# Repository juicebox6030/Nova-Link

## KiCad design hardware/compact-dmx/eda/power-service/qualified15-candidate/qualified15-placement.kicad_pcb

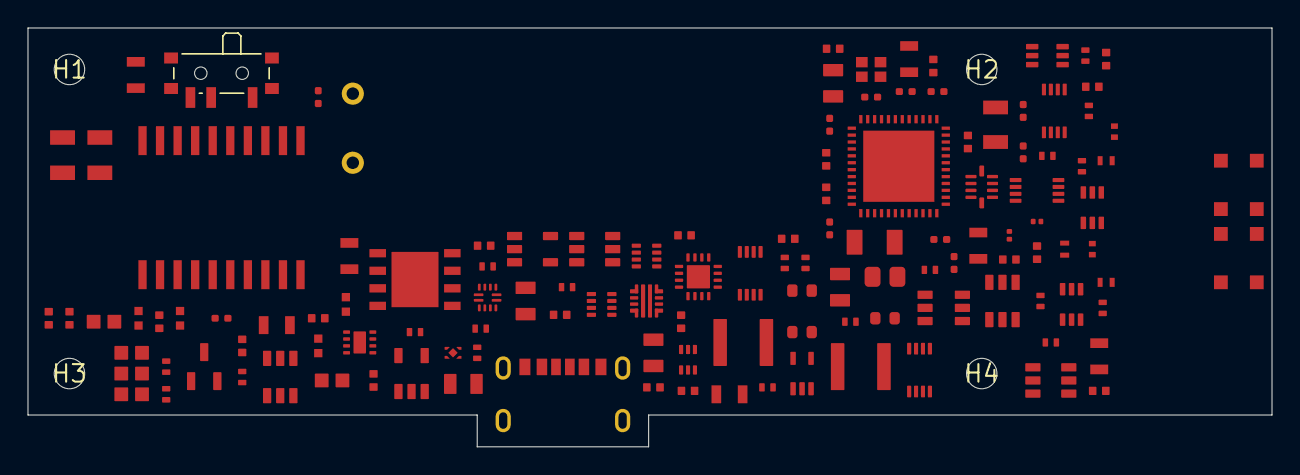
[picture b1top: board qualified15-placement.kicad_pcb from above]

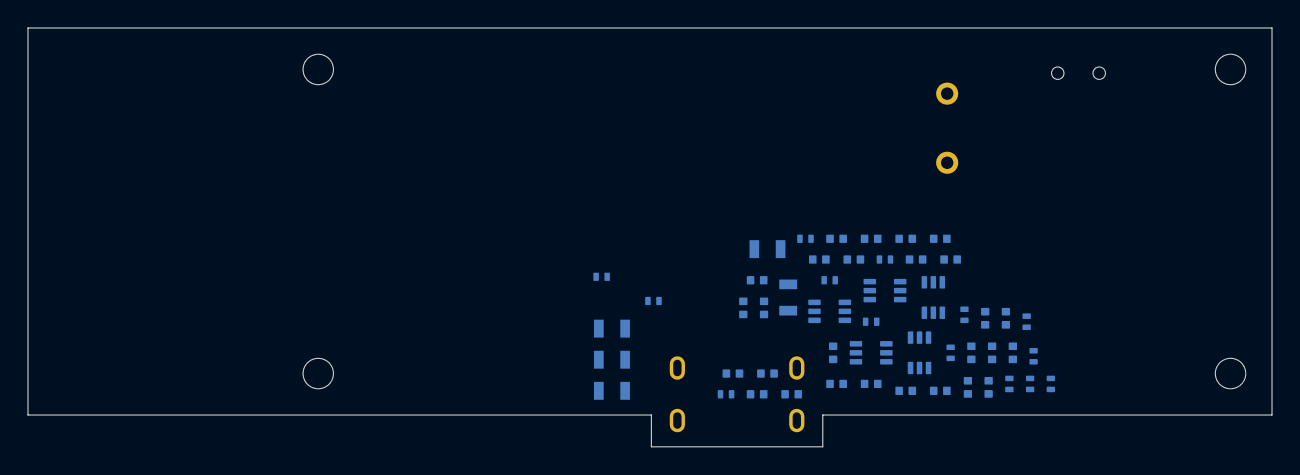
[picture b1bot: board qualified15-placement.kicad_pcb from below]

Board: 2 copper layers, 90.0 x 30.3 mm, 178 parts (51 on the bottom side), 105 nets, no tracks yet.

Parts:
BASE_A101: 0900AD47A2450001E PROTOTYPE TUNING REQUIRED; Johanson_0900AD47_IsolatedLands
BASE_C1, BASE_C3: GRM155R71E104KE14D 100nF 25V X7R; TI_CAPC1005_Vector
BASE_C2, BASE_C4: GRM21BR71A106KE51L 10uF 10V X7R; Murata_GRM21_Reflow
BASE_C101, BASE_C102: GRM188R60J226MEA0D 22uF; TI_CAPC1608_Vector
BASE_C103: GRM155R61C105KA12D 1uF; TI_CAPC1005_Vector
BASE_C104, BASE_C105, BASE_C106, BASE_C107, BASE_C108, BASE_C109: GRM155R71E104KE14D 100nF; TI_CAPC1005_Vector
BASE_C110, BASE_C111: GRM1555C1H120JA01D 12pF; TI_CAPC1005_Vector
BASE_C112, BASE_C113: GRM0335C1H101GA01D 100pF; TI_CAPC0603_Vector
BASE_C115: GJM1555C1H1R0BB01D 1.0pF TUNE; Murata_GJM155_Manufacturer
BASE_C116: GJM1555C1H8R2DB01D 8.2pF TUNE; Murata_GJM155_Manufacturer
BASE_FL101: BLM18HE152SN1D; TI_BLM18_Vector
BASE_L101: MLZ2012N6R8LT000 6.8uH; TI_MLZ2012_Vector
BASE_L102: 0402HP-2N7XGRW 2.7nH TUNE; Coilcraft_0402HP_Manufacturer
BASE_L103: 0402HP-5N1XGRW 5.1nH TUNE; Coilcraft_0402HP_Manufacturer
BASE_L104: 0402HP-12NXGRW 12nH TUNE; Coilcraft_0402HP_Manufacturer
BASE_R1, BASE_R2, BASE_R3: CRCW040210K0FKED 10k 1%; Vishay_CRCW0402
BASE_R4: CRCW04021K00FKED 1k 1%; Vishay_CRCW0402
BASE_R_TERM1, BASE_R_TERM2: CRCW1206240RFKEA 240R 1% 0.25W; Vishay_CRCW1206
BASE_S_TERM: PCM12SMTR OFF=1-2 / ON=2-3; PCM12_PENDING_MANUFACTURER_LAND_RECHECK
BASE_TR101: 0900PC15A0036001E; TI_IPC1352_Vector
BASE_U1: CC1352R1F3RGZR; TI_RGZ0048A
BASE_U5: ISOW1412DFMR; TI_DFM0020A
BASE_Y101: FC-135 32.7680KA-AG0; Epson_FC135_Manufacturer
BASE_Y102: NX2016SA 48MHz EXS00A-CS05517; NDK_NX2016SA_Manufacturer
C1, C7, C15, C16, C17, C18, C21: GRM155R61C105KA12D 1uF 16V X5R; C0402
C2, C3, C22: GRM155R71H103KA88D 10nF 50V X7R; C0402
C4, C5, C24, C25, C26, C27, C28, C29, C30, C31, C32, C33, C34, C35, C36, C37, C38, C39, C40, C41, C42, C43, C44, C45: GRM155R71E104KE14D 100nF 25V X7R; C0402
C6, C8, C9, C10, C11, C12, C13, C14, C19, C20: GRM21BR71A106KE51L 10uF 10V X7R; C0805
C23: HV1325-2R7156-R 15F 2.7V; Cell_leads
H1, H2, H3, H4: Mechanical NPTH 2.2
J1: USB4125-GF-A; USB_GCT
J4: Fabricated six-pad cJTAG/reset/ROM; VREF sense on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; Factory6
L1: XGL4020-222MEC 2.2uH 20%; L4020
L2: XFL4020-222MEC 2.2uH 20%; L4020
R1: TNPW1206150RBEEA 150ohm 0.1% 25ppm; R1206
R2: TNPW0805330RBEEA 330ohm 0.1% 25ppm; R0805
R3: TNPW040222K1BEED 22100ohm 0.1% 25ppm; R0402
R4, R6, R7, R8, R12, R13, R15, R21, R25, R27, R29, R31, R33, R35, R37, R38, R39, R40, R43, R44, R45, R46: TNPW040210K0BEED 10000ohm 0.1% 25ppm; R0402
R5: TNPW0805909KBEEA 909000ohm 0.1% 25ppm; R0805
R9: TNPW0805249KBEEA 249000ohm 0.1% 25ppm; R0805
R10: TNPW0805115KBEEA 115000ohm 0.1% 25ppm; R0805
R11: TNPW04023K32BEED 3320ohm 0.1% 25ppm; R0402
R14, R18: TNPW0402100RBEED 100ohm 0.1% 25ppm; R0402
R16, R17, R23, R41, R42, R47, R48, R56: TNPW0402100KBEED 100000ohm 0.1% 25ppm; R0402
R19: TNPW040211K9BEED 11900ohm 0.1% 25ppm; R0402
R20: TNPW040222K5BEED 22500ohm 0.1% 25ppm; R0402
R22: TNPW0805562KBEEA 562000ohm 0.1% 25ppm; R0805
R24: TNPW040232K4BEED 32400ohm 0.1% 25ppm; R0402
R26: TNPW040252K3BEED 52300ohm 0.1% 25ppm; R0402
R28, R32: TNPW040289K8BEED 89800ohm 0.1% 25ppm; R0402
R30, R34: TNPW040280K6BEED 80600ohm 0.1% 25ppm; R0402
R36: TNPW04024K70BEED 4700ohm 0.1% 25ppm; R0402
R49: TNPW040233K0BEED 33000ohm 0.1% 25ppm; R0402
R50, R51, R52, R53, R54, R55: TNPW040247K0BEED 47000ohm 0.1% 25ppm; R0402
S1: PCB normally-open SERVICE contact; Contact2
S2: PCB normally-open RESET contact; Contact2
U2: AT25SF161B-MHB-T; NOR8
U3: BQ25173DSGR; DSG8
U4: TPS62132RGTR; RGT16
U5: TPS61023DRLR; DRL6
U6: TPS259474LRPWR; RPW10
U7: TPS7A0225PDBVR; DBV5
U8, U10, U20: TPS3700DDCR; DDC6
U9: TPS3839G25DBZR; DBZ3
U16: TPS3831K33DQNR; DQN4
U17, U18: SN74LVC2G08DCUR; DCU8
U19, U40: TPS2116DRLR; DRL8
U24: TPS70933DBVR; DBV5
U25: TUSB320LAIRWBR; RWB12
U26: TPS3808G33DBVR; DBV6
U27: TPS3808G01DBVR; DBV6
U28: SN74LVC1G14DCKR; DCK5
U30, U32: SN74LVC1G11DCKR; DCK6
U31: SN74LVC1G0832DCKR; DCK6
U33, U34: SN74LVC2G132DCUR; DCU8
U35: SN74LVC1G3208DCKR; DCK6
U36, U37: SN74LVC2G17DCKR; DCK6
U38, U39: SN74LVC2G14DCKR; DCK6

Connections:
ANT_2G4: BASE_A101.1, BASE_C115.1, BASE_L102.2
ANT_915: BASE_A101.4, BASE_L104.2
AON_2V5: C17.1, C18.1, C24.1, C27.1, C28.1, C29.1, C30.1, C34.1, C35.1, C36.1, C37.1, C38.1, C39.1, C40.1, C41.1, C42.1, C43.1, R49.1, R50.1, R51.1, R52.1, R53.1, R56.1, U7.5, U8.5, U9.3, U10.5, U19.5, U20.5, U27.6, U30.5, U31.5, U32.5, U33.8, U34.8, U35.5, U36.5, U37.5, U38.5, U39.5
AON_OK: U9.2, U30.6, U32.3
AON_PRIORITY: R3.2, R4.1, U40.4
AON_RAW: C15.1, C16.1, U7.1, U7.3, U40.2, U40.7
AON_USB_LIMITED: C1.1, R2.2, R3.1, U40.3, U40.5
BACKUP_RAW: C8.1, C9.1, R30.1, U4.10, U4.11, U4.12, U19.2, U19.7
BOOST_3V9: C12.1, C13.1, R17.1, R22.1, R34.1, U5.6, U19.6, U40.6
BOOST_FB: R22.2, R23.1, U5.1
BOOST_NOT_READY_OD: R53.2, U20.6, U39.1
BOOST_READY: U31.3, U39.6
BOOST_SENSE: R34.2, R35.1, U20.4
BOOST_SW: L1.1, U5.5
BUCK_EN: R54.1, U4.13, U17.1, U35.4
BUCK_PG: BASE_U1.21, R36.2, U4.4, U33.6, U37.1
BUCK_PG_BUF: U27.3, U37.6
BUCK_SS: C22.1, U4.9
BUCK_SW: L2.1, U4.1, U4.2, U4.3
CAP_ARM: U34.6, U34.7, U35.3, U37.3
CAP_BAR: U34.2, U34.3
CAP_BOOST_EN: R55.1, U5.2, U37.4
CAP_OK: U32.1, U36.4
CAP_OK_OD: R50.2, U8.1, U36.3
CAP_POS: C14.1, C23.1, L1.2, R20.1, R24.1, R26.1, U3.8, U5.3
CAP_RESET_N: U32.4, U34.5
CAP_SAFE_PATH: U31.4, U32.6
CAP_SENSE: R24.2, R25.1, U8.3
CAP_SET_N: U33.7, U34.1
CAP_START_N_OD: R51.2, U8.6, U38.1
CAP_START_OK: U33.2, U38.6
CAP_START_SENSE: R26.2, R27.1, U8.4
CC1: J1.A5, U25.1
CC2: J1.B5, U25.2
CC_3V3: C20.1, C25.1, C26.1, C33.1, R6.1, R7.1, R8.1, R10.1, U24.5, U25.12, U26.5, U26.6, U28.5
CC_ADVERT_OK: U26.3, U28.4
CC_ALLOW: R9.1, R10.2, U6.1, U26.1, U30.3
CC_OUT1: R6.2, U25.7, U28.2
CC_OUT2: R7.2, U25.8
CC_RAW: C19.1, R1.2, U24.1, U24.3
CC_VBUS_DET: R5.2, U25.4
CHARGE_DISABLE: R56.2, U3.3, U33.3
DCDC_SW: BASE_L101.1, BASE_U1.33
DCOUPL: BASE_C103.1, BASE_U1.23
DMX_DE_SAFE: BASE_R1.1, BASE_U5.3, U17.3
DMX_N: BASE_R_TERM1.2, BASE_R_TERM2.2, BASE_U5.18, BASE_U5.19
DMX_P: BASE_S_TERM.2, BASE_U5.17, BASE_U5.20
DMX_POWER_EN: BASE_R3.1, BASE_R4.1, U18.7
EFUSE_DVDT: R14.1, U6.7
EFUSE_DVDT_C: C2.1, R14.2
EFUSE_ILM: R11.1, U6.9
EFUSE_PGTH: R12.2, R13.1, U6.4
EFUSE_TIMER: C3.1, U6.10
FLASH_HOLD_N: R46.2, U2.7
FLASH_WP_N: R45.2, U2.3
GND_ISO: BASE_C3.2, BASE_C4.2, BASE_U5.11, BASE_U5.13, BASE_U5.14, BASE_U5.15
GND_USB: BASE_C1.2, BASE_C2.2, BASE_C101.2, BASE_C102.2, BASE_C103.2, BASE_C104.2, BASE_C105.2, BASE_C106.2, BASE_C107.2, BASE_C108.2, BASE_C109.2, BASE_C110.2, BASE_C111.2, BASE_C113.2, BASE_C115.2, BASE_C116.2, BASE_L103.2, BASE_R1.2, BASE_R3.2, BASE_TR101.2, BASE_TR101.3, BASE_TR101.10, BASE_U1.49, BASE_U5.6, BASE_U5.10, BASE_Y102.2, BASE_Y102.4, C1.2, C2.2, C3.2, C4.2, C5.2, C6.2, C7.2, C8.2, C9.2, C10.2, C11.2, C12.2, C13.2, C14.2, C15.2, C16.2, C17.2, C18.2, C19.2, C20.2, C21.2, C22.2, C23.2, C24.2, C25.2, C26.2, C27.2, C28.2, C29.2, C30.2, C31.2, C32.2, C33.2, C34.2, C35.2, C36.2, C37.2, C38.2, C39.2, C40.2, C41.2, C42.2, C43.2, C44.2, C45.2, J1.A12, J1.B12, J1.SH, J4.2, R4.2, R8.2, R9.2, R11.2, R13.2, R15.2, R16.2, R17.2, R19.2, R21.2, R23.2, R25.2, R27.2, R29.2, R31.2, R33.2, R35.2, R41.2, R42.2, R47.2, R48.2, R54.2, R55.2, S1.2, S2.2, U2.4, U2.9, U3.4, U3.9, U4.5, U4.6, U4.7, U4.8, U4.15, U4.16, U4.17, U5.4, U6.2, U6.8, U7.2, U8.2, U9.1, U10.2, U16.3, U16.5, U17.4, U18.4, U18.5, U18.6, U19.1, U20.2, U24.2, U25.3, U25.10, U25.11, U26.2, U27.2, U28.3, U30.2, U31.2, U32.2, U33.4, U34.4, U35.2, U36.2, U37.2, U38.2, U39.2, U39.3, U40.1
ICHG_FILTER: C4.1, R18.2, R19.1
ICHG_PIN: R18.1, U3.2
ISOW_EN_PIN: BASE_R4.2, BASE_U5.8
ISO_3V3: BASE_C3.1, BASE_C4.1, BASE_U5.12, BASE_U5.16
LIMITED_5V: C6.1, C7.1, R12.1, R16.1, R28.1, U3.1, U6.6, U19.3
MAIN_NOT_READY_OD: R52.2, U10.6, U38.3
MAIN_READY: U31.1, U35.6, U38.4
MAIN_SENSE: R30.2, R31.1, U10.4
MANUAL_RESET_N: J4.5, R38.2, S2.1, U16.2
MCU_DE_REQUEST: BASE_U1.10, R41.1, U17.5
MCU_DMX_RX: BASE_U1.18, BASE_U5.4
MCU_DMX_TX: BASE_U1.19, BASE_U5.2
MCU_ISO_REQUEST: BASE_U1.11, R42.1, U18.1
MCU_RE_N: BASE_R2.2, BASE_U1.12, BASE_U5.5, R43.2
MCU_VDDR: BASE_C102.1, BASE_C108.1, BASE_C109.1, BASE_L101.2, BASE_U1.45, BASE_U1.48
MCU_VDDS: BASE_C101.1, BASE_C104.1, BASE_C105.1, BASE_C106.1, BASE_C107.1, BASE_FL101.1, BASE_U1.13, BASE_U1.22, BASE_U1.34, BASE_U1.44
RAW_SENSE: R32.2, R33.1, U20.3
RESET_OK: BASE_U1.35, U16.1, U17.2
RF_2G4_50: BASE_L102.1, BASE_TR101.1
RF_915_50: BASE_C112.2, BASE_C116.1, BASE_L103.1, BASE_L104.1
RF_915_UNBLOCKED: BASE_C112.1, BASE_TR101.4
RF_N_2_4GHZ: BASE_TR101.8, BASE_U1.2
RF_N_SUB_1GHZ: BASE_TR101.6, BASE_U1.4
RF_P_2_4GHZ: BASE_TR101.9, BASE_U1.1
RF_P_SUB_1GHZ: BASE_TR101.7, BASE_U1.3
ROM_BOOT_STRAP: BASE_U1.8, J4.6, R40.2
RX_TX: BASE_C113.1, BASE_TR101.5, BASE_U1.5
SERVICE_N_DISTINCT_GPIO: BASE_U1.9, R39.2, S1.1
SOURCE_SENSE: U30.1, U36.6
SOURCE_SENSE_OD: R49.2, U6.3, U10.1, U20.1, U36.1
SOURCE_VALID: U19.4, U27.5, U30.4, U31.6, U33.1, U33.5, U35.1
SPI_CS_N: BASE_U1.17, R44.2, U2.1
SPI_MISO: BASE_U1.14, U2.2
SPI_MOSI: BASE_U1.15, R48.1, U2.5
SPI_SCK: BASE_U1.16, R47.1, U2.6
SYS_3V3: BASE_C1.1, BASE_C2.1, BASE_FL101.2, BASE_R2.1, BASE_U5.1, BASE_U5.9, C10.1, C11.1, C21.1, C31.1, C32.1, C44.1, C45.1, J4.1, L2.2, R36.1, R37.1, R38.1, R39.1, R40.1, R43.1, R44.1, R45.1, R46.1, U2.8, U4.14, U16.4, U17.8, U18.8
SYS_READY: U17.6, U17.7, U18.2
TCKC: BASE_U1.25, J4.4
TERM_SW: BASE_R_TERM1.1, BASE_R_TERM2.1, BASE_S_TERM.3
TMSC: BASE_U1.24, J4.3
USB_SENSE: R28.2, R29.1, U10.3
VBUS_GOOD_3V3: BASE_U1.20, R37.2, U27.1
VBUS_RAW: C5.1, J1.A9, J1.B9, R1.1, R2.1, R5.1, R15.1, R32.1, U6.5
VCHG_FB: R20.2, R21.1, U3.7
X32K_Q1: BASE_C110.1, BASE_U1.6, BASE_Y101.1
X32K_Q2: BASE_C111.1, BASE_U1.7, BASE_Y101.2
X48M_N: BASE_U1.46, BASE_Y102.3
X48M_P: BASE_U1.47, BASE_Y102.1

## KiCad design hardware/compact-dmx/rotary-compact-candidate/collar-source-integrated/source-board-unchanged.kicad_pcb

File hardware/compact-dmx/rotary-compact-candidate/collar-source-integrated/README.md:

# AXIAL-R1 source integrated into repaired collar

This is the bounded mechanical integration of the frozen routed source and repaired collar, in this directory only. The routed PCB is unchanged. Current evidence is in `receipt.json`, `verification.log`, the individual check JSON files, editable `build.py`/`integrated.FCStd`, six assembled STEP poses, exploded STEP and dimensioned SVG/PDF drawings. Geometric prototype acceptance is distinct from electrical, flex, strength, safety or manufacturing qualification.

The earlier repair instructions quoted in the frozen `mechanism-repaired/README.md` were the **parent/root repair brief**, not owner-verbatim wording. That historical folder is unchanged. The owner's compactness, stationary mains/PE, isolated-LV-only rotation, positive locking and 180-degree bounded motion objectives remain. No source-board circuit, baseline CAD, BOM, canonical documentation, mains or other worker's files are edited. HEAD is b42c0e6284aac734fde851c69146abf73920f337; no publication or hardware activity is authorized or performed.

## Actual source placement and envelope

The source is AXIAL-R1, board SHA256 `53b83aa71d1bcd986906509348bc061eb9e334296ddc980340c954eb8305cbcc`. It has34 footprints:32 purchased components plus J0 fabricated flex lands and TP1 zero-height copper probe. Source CAD contains33 body/land allocations plus the actual-hole PCB, four swept stake allocations, and four assembly reserves. **All42 saved source shapes** are transformed, compared independently by inverse-transform symmetric difference, and retained. TP1 has no invented package height; its actual copper remains in the unchanged KiCad board and copper check. These are the source's conservative package/slot allocations, not manufacturer detailed solid models.

The proper-handed rotation is X-axis−90 degrees, followed by translation(75,26.1,10):

`Xglobal=75+Xlocal; Yglobal=26.1+Zlocal; Zglobal=10−Ylocal`, determinant+1.

PCB: X75..102, Y25.1..26.1, Z−10..10mm. Its98 actual holes and four connector stake allocations are preserved. The maximum connector allocation ends atX104.17. This is **not an exact supplier mating plane**. The shell ends atX102, at the actual PCB-edge datum. The Ø48×142 stationary core is unchanged; collar OD remains66. Locked span grows from67.8 to **73.17mm** (X31..104.17); released span from72.0 to **77.37mm** (X26.8..104.17). The finite engineering plug screen ends atX116.17, within the core's142mm axial envelope. No endcap/fixture or universal cable fit follows from that fact.

The source's full3.46mm component height, top reserve through3.71mm, bottom reserve through−1.35mm and external FPC/tool reserves replace every previous source placeholder. The actual routed source is physically allocated; its functional acceptance remains unmet. The source's four known GCT NPTH process errors, startup/current/thermal/fault and supplier-profile gates are retained.

## Supports, retention and tolerances

The positive rotor half incorporates two dielectric edge rails and webs to the shell. Their seating strips overlap only the outer0.20mm of the PCB's Y edges. The independent KiCad check reads the actual saved pads, all tracks/vias and filled-zone outlines: minimum nominal copper clearance from these strips is0.3005mm; all98 holes clear them. There are no new PCB holes, no contact on exposed pads and no conductive heat-spreader assumption.

Sidewalls have20.2mm clear span; proposed PCB width20.0±0.1 leaves at most±0.15mm lateral float. With additional0.03mm rail and0.05mm PCB copper/edge process allocations, the nominal copper gap retains **0.0705mm**. These are proposed manufacturing tolerances, not supplier capability evidence. Top capture has1.24mm seat-to-lip clearance for PCB1.0±0.1; allocating0.03mm to each rail surface leaves0.08mm minimum normal assembly clearance. The0.50mm capture lip covers the full opposite edge and the final6mm of the FPC-exit edge (X96..102), leaving the ribbon exit open. Laminate edge pressure, bow, fretting, insertion force, clip deflection, polymer creep and shock remain tests.

A separate end retainer atX102..103 is held by two external M1 screw envelopes atZ±11,Y25.65. Their1.5mm pilot engagement is bounded in the collision checks. The PCB slides along+X with the retainer removed;33 positions and four structural obstacles give132 insertion checks. An additional152 bounding-prism checks cover the continuous32mm translation between samples, conservatively filling source holes. The retainer does not cover the IC tops or contact routed copper. All screw dimensions are prototype engineering choices; approved fastener/thread material and allowable torque remain open.

The source end has no insulating blanket above the converters. Actual per-package radial airspace to the shell ID is reported in `source-contract.json`; the3.71mm assembly reserve also clears the structure outside the explicit edge support interfaces. No rated thermal path or sealed-enclosure temperature is inferred. The solder-access slot and driver passages are real openings; guard/sealing/ingress qualification remains open.

## Static fanout and termination

`StaticDevelopedFanout` is a separate **~183.69mm** static extension; it does not alter the1046.167655992167mm active rotary path or its181-position numerical proof. It follows a generalized cylindrical surface: every transverse ruling is parallel to globalX, while the YZ cross-section curves. Flattening maps arc length into the second planar coordinate; shifting the axial trim center fromX57 to85.5 is a cut-pattern change, not material stretch or ribbon twist. `fanout-flat.svg` and `fanout-proof.json` give editable developed artwork, two true-normal8mm traces and1mm separation. The ruled CAD sections are finite geometric approximations of the analytic intended profile, not supplier tooling surfaces.

The static route leaves the moving tail at its exact0.3rad end slope, smoothly moves toR31.6, then uses anR2.5 terminal bend into the planar source tongue. The proposed total stack is0.16mm with70µm rolled-annealed copper, the same material class as the active ribbon. Minco's cached2019 guide PDFp8 describes polyimide flex/material/bend-to-install considerations; All Flex's cached primary bend guide p1 identifies RA foil and6× composite thickness as a starting point for one/two-layer designs. R2.5 is the neutral-surface radius; inside radius2.42 is15.125× the proposed stack. This is **not supplier approval of this70µm stack, formed shape, solder process, vibration or lifetime**. No plated features are added in the active bend.

A real dielectric saddle supports the inside of the terminal bend with allocated clearance and stops atZ−10.3 before the PCB edgeZ−10. The covered ribbon is clamped atZ−14..−12 between baseY25.8..26.4 and shoeY26.56..27.5. Two M1 clamp screws atX74.4/96.6,Z−13 have0.6mm nominal pilot engagement. Their driver passages are modeled. The saddle, clamp and outer-shell channel control the static path; the active dynamic winding still requires physical equilibrium/guide/friction testing. The added channel passes around the existing frame; a connected bridge retains the integral stop outside the static ribbon path.

The existing J0 **land/joint allocation** of0.30mm is retained without pretending it is a purchased connector. Proposed source tongue bottom/top areY26.40/26.56. The exposed conductor ends occupy the two actual rounded8×2mm pad regions (cornerR0.2) overZ−9.4..−7.4. J0.1 at local(6,18.4), globalX81, is `/FPC_5V`; J0.2 at local(15,18.4), globalX90, is `/GND_ISO`. The corresponding active-width trace centers areX52.5 and61.5. Bare-copper face orientation, polarity marking and nonbridging solder fillets must be inspected during assembly. The0.30mm envelope is a **proposed solder/land height budget**, not a measured or manufacturer-recommended joint thickness. Paste/preform volume, wetting, copper finish, solder alloy/process and peel strength remain assembly qualification gates. No claim of a completed electrically qualified flex assembly is made.

The static extension adds approximately14.20mΩ loop resistance at85°C using rho20=.01724Ω·mm²/m and alpha=.00393/K. At2.987A this adds42.4mV upstream of the converter and0.127W before additional joint resistance; this is not a direct subtraction from regulated USB VBUS. A proposed63µm minimum copper /+3% resistivity allocation gives about16.25mΩ; that allocation is not a sourced supplier tolerance. **The source power budget must be revised**; this loss must not be silently absorbed into the already narrow source margin. The calculation is an incremental copper screen, not a current/temperature guarantee. The existing source4.786V lower conditional result is not recomputed or upgraded by this mechanical task.

## Assembly sequence and checks

1. Manufacture/inspect the two connected rotor halves, stationary spool, rails, forming saddle, channel, integral-stop bridge, retainer and clamp. Qualify proposed dielectric material/process (PEEK-class prototype allocation; no sourced allowable claimed). Assemble the unchanged stationary bonds, guides, captive index spring/pin/cap and fixed flex clamp per the frozen mechanism procedure.
2. Attach the moving-tail stiffener/ear stack to the positive rotor subassembly before core insertion, using the retained inward tool passages. Preform the static tail to the developed pattern; do not force a flat rectangular ribbon into the shifted pattern.
3. Slide the unchanged source PCB into the edge rails from+X and install the external end retainer. Lay the static tongue on the J0 land/joint allocation, establish polarity, and solder through the20.8×2.8mm shell access slot. Solder-tool geometry is checked above the target joint; thermal damage and process are not simulated.
4. Seat the terminal bend on the saddle and install the external clamp. Verify covered flex, not exposed solder, is compressed. Thread/preload values require prototype qualification. The other rotor half closes around the formed fanout; frame-driver paths remain clear even in the assembled geometry.
5. Exercise the captive release and all13 positions only after physical authorization and qualified assembly. No hardware exercise was performed here. Source attach/startup/current/fault tests remain separate electrical work.

`checks.json` enumerates every physical pair at−90/0/+90 in both lock states; only14 named, numerically bounded thread interfaces permit positive overlap. Source package and stake allocations are not excluded. Alternate flex poses, purpose-labeled assembly reserves and plug test volume are separate from simultaneous parts. `source-contract.json` tests those reserves and plug volume explicitly. `access.json` checks16 staged tool paths. `motion-check.json` recomposes181 released states: every added solid clears a stronger full-revolution stationary envelope; unchanged fixed/lock shapes and index region are independently compared to the frozen original. The original181 rigid-motion proof plus its containment proof remains applicable to retained geometry. This avoids pretending that an old proof alone checks new source hardware. Active ribbon geometry is unchanged and checked against the complete assembly at three poses. `active_identity.py` compares every complete straight-edge planar boundary:4,100 faces per pose, at1e-9mm coordinate rounding, with area/volume consistency. Raw BRep bytes are not canonical across serialization; no byte-identity claim substitutes for this geometric check. Run that identity check before `motion_check.py`.

Final saved FCStd and all exported STEP shapes are independently reopened for valid, connected closed solids. Source-board bytes and both frozen folders are checked against `frozen-inputs.json`; the verifier does not refresh input hashes. Geometry acceptance does not resolve supplier flex equilibrium/endurance, static profile stability, spring return, torque/strength, PCB/support tolerances, solder/thermal/current, source faults, connector profile, endcap/fixture or mains/PE/barrier certification.

## Reproduce locally

Use the existing FreeCAD1.1.3, KiCad10.0.7 Flatpak, Python/NumPy/ReportLab and pdftoppm. From this directory, run `build.py`, `check_export.py`, `motion_check.py`, `source_contract.py`, `access.py`, `contacts.py`, `active_identity.py` and `reopen.py` with `QT_QPA_PLATFORM=offscreen /home/juicebox/.local/bin/freecadcmd <script>`. Run `flatpak run --command=python3 org.kicad.KiCad <absolute-path>/copper-check.py`; it reads but never saves the PCB. Run `python fanout.py`, `python draw.py`, render both PDFs with pdftoppm and inspect them, then `python verify.py`. Check structured outputs, not FreeCAD exit status alone. Serialization may change artifact hashes on deliberate regeneration; review the results before issuing a new receipt. Never rerun `freeze.py` to hide an input mutation.

The actual saved-file reopen was partitioned into three independent local processes with `REOPEN_GROUP=0`, `1`, `2`; `python combine_reopen.py` checks identical native/thread proofs and all eight unique STEP files. `write_receipt.py` refuses to issue a receipt unless all structured checks pass and frozen hashes still match.

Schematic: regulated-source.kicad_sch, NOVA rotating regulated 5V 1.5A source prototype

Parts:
C1, C2, C9: GRM21BC71E106ME11L 10uF; C0805
C3, C7: TMK107BBJ106MA-T 10uF; C0603
C4, C5, C6: GRM21BC81C226ME44L 22uF; C0805
C8: T520D157M010ATE055 150uF; T520D
C10, C11, C13: TMK105B7104MV-FR 100nF; C0402
C12: GRM155R71E103KA01D 10nF; C0402
D1: TPD1E10B06DPYR; DPY2
J0: FABRICATED_FPC20_SOLDER_LANDS; FPC20
J1: USB4105-GF-A; USB4105
L1: XFL4020-152MEC 1.5uH; XFL4020
R1: TNPW040224K9BYED 24900ohm; R0402
R2, R4, R7: TNPW040210K0BYED 10000ohm; R0402
R3: TNPW040237K4BYED 37400ohm; R0402
R5: TNPW04021K00BYED 1000ohm; R0402
R6: TNPW040254K2BYED 54200ohm; R0402
R8, R9, R10, R11: TNPW0402100KBYED 100000ohm; R0402
TP1: FAB_FAULT_PROBE; TP1
U1: TPS259474LRPWR; RPW10
U2: TPS63070RNMR; RNM15
U3: TPS25810RVCR; RVC20

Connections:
FPC_5V: C13.1, J0.1 (STATIONARY_IRM20_PLUS_VIA_FPC), R1.1, R3.1, U1.5 (IN)
GND_ISO: C1.2, C2.2, C3.2, C4.2, C5.2, C6.2, C7.2, C8.2, C9.2, C10.2, C11.2, C12.2, C13.2, D1.2, J0.2 (ISOLATED_RETURN_VIA_FPC), J1.A1_B12 (GND_shared_land), J1.B1_A12 (GND_shared_land), J1.S1 (SHELL), J1.S2 (SHELL), J1.S3 (SHELL), J1.S4 (SHELL), R2.2, R4.2, R5.2, R7.2, R9.2, U1.4 (PGTH_UNUSED), U1.8 (GND), U2.1 (PS_SYNC_LOW_FORCED_PWM), U2.4 (GND), U2.10 (PGND), U2.15 (VSEL_LOW), U3.8 (CHG_HI_LOW), U3.12 (GND), U3.21 (EP_GND)
INPUT_ILM: R5.1, U1.9 (ILM)
INPUT_OVLO: R3.2, R4.1, U1.2 (OVLO)
INPUT_UVLO: R1.2, R2.1, U1.1 (EN_UVLO)
PORT_FAULT_OD: R11.2, TP1.1, U3.1 (FAULT_N)
REF: R10.1, U3.10 (REF)
REF_RTN: R10.2, U3.9 (REF_RTN)
REG_5V136: C4.1, C5.1, C6.1, C7.1, C8.1, C10.1, R6.1, R8.1, R11.1, U2.7 (VOUT), U2.8 (VOUT), U3.2 (IN1), U3.3 (IN1), U3.4 (IN2), U3.5 (AUX), U3.7 (CHG_HIGH)
REG_FB: R6.2, R7.1, U2.5 (FB)
REG_READY_OD: R8.2, R9.1, U2.2 (PG), U3.6 (EN)
REG_VAUX: C11.1, U2.3 (VAUX_NO_EXTERNAL_LOAD)
SW_L1: L1.1, U2.11 (L1)
SW_L2: L1.2, U2.9 (L2)
USB_CC1: J1.A5 (CC1), U3.11 (CC1)
USB_CC2: J1.B5 (CC2), U3.13 (CC2)
USB_D_SHORT: J1.A6 (D_PLUS), J1.A7 (D_MINUS), J1.B6 (D_PLUS), J1.B7 (D_MINUS)
USB_VBUS: C9.1, D1.1, J1.A4_B9 (VBUS_shared_land), J1.B4_A9 (VBUS_shared_land), U3.14 (OUT), U3.15 (OUT)

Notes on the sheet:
PROTOTYPE: stationaryIRM20-5/FPC input only. No mains/PE or module circuitry captured here. All physical source board parts shown.
U1 reverse-blocking input, UVLO/OVLO and latched circuit-breaker. U2 forcedPWM5.136V, PG enables U3 after unloaded startup; no firmware.
U3 CHG=REG5V, CHG_HI=GND:1.5A only. CC1/CC2 independent. No USBdata processing or PD voltage escalation.
J1 has16 contacts but12 shared signal lands +4shell stakes, per originalGCTB4. D+ and D- tied by copper; no invented separate ground/VBUS pads.
Bulk150uF+76uFceramic before cold socket switch. ESR/capacitance attemperature, startup/inrush/thermal/ripple/faults remain physical gates.
Shell tiedisolatedGND proposal. No rotatingPE; accessiblemetal bonding/mainsendcap/harness/safety remain parent scope.
Connector height3.31+/-0.15mm EXCEEDS3.2mm target. Placement is unrouted; no collar fit, USBcompliance or manufacturingrelease claim.

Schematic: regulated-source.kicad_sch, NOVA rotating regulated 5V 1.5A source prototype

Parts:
C1, C2, C9: GRM21BC71E106ME11L 10uF; C0805
C3, C7: TMK107BBJ106MA-T 10uF; C0603
C4, C5, C6: GRM21BC81C226ME44L 22uF; C0805
C8: T520D157M010ATE055 150uF; T520D
C10, C11, C13: TMK105B7104MV-FR 100nF; C0402
C12: GRM155R71E103KA01D 10nF; C0402
D1: TPD1E10B06DPYR; DPY2
J0: FABRICATED_FPC20_SOLDER_LANDS; FPC20
J1: USB4105-GF-A; USB4105
L1: XFL4020-152MEC 1.5uH; XFL4020
R1: TNPW040224K9BYED 24900ohm; R0402
R2, R4, R7, R12: TNPW040210K0BYED 10000ohm; R0402
R3: TNPW040237K4BYED 37400ohm; R0402
R5: TNPW04021K00BYED 1000ohm; R0402
R6: TNPW040254K2BYED 54200ohm; R0402
R8, R9, R10, R11: TNPW0402100KBYED 100000ohm; R0402
R13: TNPW0402100RBYED 100ohm; R0402
TP1: FAB_FAULT_PROBE; TP1
U1: TPS259474LRPWR; RPW10
U2: TPS63070RNMR; RNM15
U3: TPS25810RVCR; RVC20

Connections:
FPC_5V: C13.1, J0.1 (STATIONARY_IRM20_PLUS_VIA_FPC), R1.1, R3.1, U1.5 (IN)
GND_ISO: C1.2, C2.2, C3.2, C4.2, C5.2, C6.2, C7.2, C8.2, C9.2, C10.2, C11.2, C12.2, C13.2, D1.2, J0.2 (ISOLATED_RETURN_VIA_FPC), J1.A1_B12 (GND_shared_land), J1.B1_A12 (GND_shared_land), J1.S1 (SHELL), J1.S2 (SHELL), J1.S3 (SHELL), J1.S4 (SHELL), R2.2, R4.2, R5.2, R7.2, R9.2, U1.4 (PGTH_UNUSED), U1.8 (GND), U2.1 (PS_SYNC_LOW_FORCED_PWM), U2.4 (GND), U2.10 (PGND), U2.15 (VSEL_LOW), U3.8 (CHG_HI_LOW), U3.12 (GND), U3.21 (EP_GND)
INPUT_ILM: R5.1, U1.9 (ILM)
INPUT_OVLO: R3.2, R4.1, U1.2 (OVLO)
INPUT_UVLO: R1.2, R2.1, U1.1 (EN_UVLO)
PORT_FAULT_OD: R11.2, TP1.1, U3.1 (FAULT_N)
REF: R10.1, U3.10 (REF)
REF_RTN: R10.2, U3.9 (REF_RTN)
REG_5V136: C4.1, C5.1, C6.1, C7.1, C8.1, C10.1, R6.1, R8.1, R11.1, U2.7 (VOUT), U2.8 (VOUT), U3.2 (IN1), U3.3 (IN1), U3.4 (IN2), U3.5 (AUX), U3.7 (CHG_HIGH)
REG_FB: R6.2, R7.1, U2.5 (FB)
REG_READY_OD: R8.2, R9.1, U2.2 (PG), U3.6 (EN)
REG_VAUX: C11.1, U2.3 (VAUX_NO_EXTERNAL_LOAD)
SW_L1: L1.1, U2.11 (L1)
SW_L2: L1.2, U2.9 (L2)
USB_CC1: J1.A5 (CC1), U3.11 (CC1)
USB_CC2: J1.B5 (CC2), U3.13 (CC2)
USB_D_SHORT: J1.A6 (D_PLUS), J1.A7 (D_MINUS), J1.B6 (D_PLUS), J1.B7 (D_MINUS)
USB_VBUS: C9.1, D1.1, J1.A4_B9 (VBUS_shared_land), J1.B4_A9 (VBUS_shared_land), U3.14 (OUT), U3.15 (OUT)

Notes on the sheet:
PROTOTYPE: stationaryIRM20-5/FPC input only. No mains/PE or module circuitry captured here. All physical source board parts shown.
U1 reverse-blocking input, UVLO/OVLO and latched circuit-breaker. U2 forcedPWM5.136V, PG enables U3 after unloaded startup; no firmware.
U3 CHG=REG5V, CHG_HI=GND:1.5A only. CC1/CC2 independent. No USBdata processing or PD voltage escalation.
J1 has16 contacts but12 shared signal lands +4shell stakes, per originalGCTB4. D+ and D- tied by copper; no invented separate ground/VBUS pads.
Bulk150uF+76uFceramic before cold socket switch. ESR/capacitance attemperature, startup/inrush/thermal/ripple/faults remain physical gates.
Shell tiedisolatedGND proposal. No rotatingPE; accessiblemetal bonding/mainsendcap/harness/safety remain parent scope.
R12=10k EN series perTI11.1; R13=100ohm DVDT series perTI7.3.5.1, C12max11nF. Connector maxheight3.46mm; no fit/release claim.

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
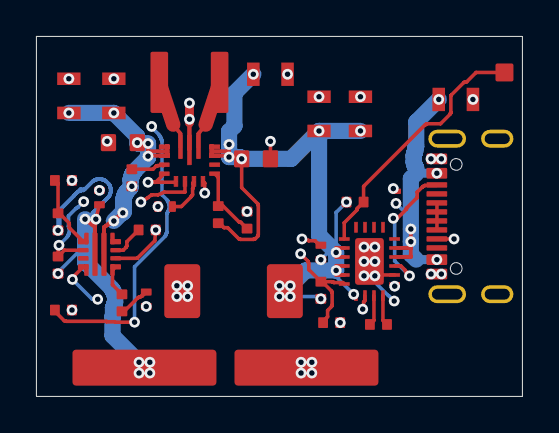
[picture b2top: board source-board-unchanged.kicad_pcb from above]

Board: 4 copper layers, 27.0 x 20.0 mm, 34 parts (0 on the bottom side), 22 nets.

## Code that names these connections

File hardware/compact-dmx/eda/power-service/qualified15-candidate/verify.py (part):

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old_root=E.parse(P/'history/pre-u40-fix-qualified15.net')
old_pins={x.attrib['ref']+'.'+x.attrib['pin']:n.attrib['name'].rsplit('/',1)[-1] for n in old_root.findall('./nets/net') for x in n}
pin_changes=[[k,old_pins.get(k),pins.get(k)] for k in sorted(old_pins.keys()|pins.keys()) if old_pins.get(k)!=pins.get(k)]
assert pin_changes==[['U40.5','GND_USB','AON_USB_LIMITED']],pin_changes
G='GND_USB';A='AON_2V5'
# Exact core pinouts incl exposed pads. None must be an explicit NC.
expected={
'U40':{1:G,2:'AON_RAW',3:'AON_USB_LIMITED',4:'AON_PRIORITY',5:'AON_USB_LIMITED',6:'BOOST_3V9',7:'AON_RAW',8:None},
'U6':{1:'CC_ALLOW',2:G,3:'SOURCE_SENSE_OD',4:'EFUSE_PGTH',5:'VBUS_RAW',6:'LIMITED_5V',7:'EFUSE_DVDT',8:G,9:'EFUSE_ILM',10:'EFUSE_TIMER'},
'U3':{1:'LIMITED_5V',2:'ICHG_PIN',3:'CHARGE_DISABLE',4:G,5:None,6:None,7:'VCHG_FB',8:'CAP_POS',9:G},
'U5':{1:'BOOST_FB',2:'CAP_BOOST_EN',3:'CAP_POS',4:G,5:'BOOST_SW',6:'BOOST_3V9'},
'U19':{1:G,2:'BACKUP_RAW',3:'LIMITED_5V',4:'SOURCE_VALID',5:A,6:'BOOST_3V9',7:'BACKUP_RAW',8:None},
'U4':{1:'BUCK_SW',2:'BUCK_SW',3:'BUCK_SW',4:'BUCK_PG',5:G,6:G,7:G,8:G,9:'BUCK_SS',10:'BACKUP_RAW',11:'BACKUP_RAW',12:'BACKUP_RAW',13:'BUCK_EN',14:'SYS_3V3',15:G,16:G,17:G},
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assert set(ps)=={r for r in comps if re.fullmatch('[RCDLS][0-9]+',r)}
for ref,(v,a,b) in ps.items():assert (comps[ref],pins[ref+'.1'],pins[ref+'.2'],types[ref+'.1'],types[ref+'.2'])==(v,a,b,'passive','passive'),ref
mcu=['SYS_3V3',G,'MCU_DMX_TX','MCU_DMX_RX','MCU_DE_REQUEST','MCU_RE_N','MCU_ISO_REQUEST','SPI_CS_N','SPI_MOSI','SPI_SCK','SPI_MISO','VBUS_GOOD_3V3','SERVICE_N_DISTINCT_GPIO','ROM_BOOT_STRAP','RESET_OK','TMSC','TCKC','BUCK_PG']
dmx=['SYS_3V3',G,'MCU_DMX_TX','DMX_DE_SAFE','MCU_RE_N','MCU_DMX_RX','DMX_POWER_EN']
for ref,ns in [('J2',mcu),('J3',dmx),('J4',['SYS_3V3',G,'TMSC','TCKC','MANUAL_RESET_N','ROM_BOOT_STRAP'])]:
 for i,n in enumerate(ns):assert pins[ref+'.'+str(i+1)]==n
assert comps['J1']=='USB4125-GF-A'
for no,n in {'A5':'CC1','B5':'CC2','A9':'VBUS_RAW','B9':'VBUS_RAW','A12':G,'B12':G,'SH':G}.items():assert pins['J1.'+no]==n
assert {k.split('.')[1] for k in pins if k.startswith('J1.')}=={'A5','B5','A9','B9','A12','B12','SH'}
assert not any(n=='INPUT_FAULT_N' for n in pins.values()) # no invented MCU fault translator
assert not any('TPS61094' in v or 'TPS2553' in v for v in comps.values())
assert pins['U5.3']==pins['U3.8']=='CAP_POS'
assert pins['U24.1']=='CC_RAW' and pins[byrole['R_CC_FEED']+'.1']=='VBUS_RAW'
# Actual exported outputs are the physical wired-AND, not a fabricated logic box.
assert {k for k,n in pins.items() if n=='SOURCE_SENSE_OD' and types[k]=='open_collector'}=={'U6.3','U10.1','U20.1'}
assert pins['U28.5']==pins['U26.5']==pins['U26.6']=='CC_3V3'
assert pins['U26.1']==pins['U6.1']=='CC_ALLOW' and pins['U26.3']=='CC_ADVERT_OK'
# Evaluate actual exported gates; latch is solved as state, not a fake digital input.
comb=[]
for r,v in comps.items():
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  ex['AON_OK']=True # only after the actual supervisor's reset release
 e,q=settle(ex,armed)
 assert e['SOURCE_VALID']==(source_ok and cc_ok)
 if label=='cold source':assert e['BUCK_EN'] and not q and e['CHARGE_DISABLE']
 if not armed and not e['SOURCE_VALID']:assert not q and not e['CAP_BOOST_EN'] and not e['BUCK_EN']
 physical.append({'scenario':label,'U40_selection':choice,'conditional_AON_input_V':supply,'SOURCE_VALID':e['SOURCE_VALID'],'CAP_ARM':q,'BUCK_EN':e['BUCK_EN']})
# eFuse latch is not cleared by its own PG/output collapse: pin1 is CC_ALLOW.
assert pins['U6.1']=='CC_ALLOW' and all('SOURCE_VALID' not in ns for op,ns,y in comb if y=='CC_ALLOW')
# Stable-source status supervisor pin contract: actual source + buffered buckPG,
# delayed assertion after both; asynchronous low on either, no timed good override.
assert pins['U27.5']=='SOURCE_VALID' and pins['U27.3']=='BUCK_PG_BUF' and pins['U27.1']=='VBUS_GOOD_3V3'
viol=[v for sh in json.loads((P/'erc.json').read_text())['sheets'] for v in sh['violations']];assert not viol,viol
rows=list(csv.DictReader((P/'component-ledger.csv').open()));area=sum(float(r['body_area_mm2']) for r in rows if r['kind']=='physical')
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
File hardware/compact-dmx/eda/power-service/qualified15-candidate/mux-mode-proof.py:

"""Independent TPS2116 behavioral regression, not imported from the generator.

Primary: cached TI SLVSFG1A, sections 6.1/6.3/6.5/7.3.1/7.3.2/7.4.
Topology matters: MODE physically tied VIN1 is priority mode, not the
external-bias manual mode evaluated merely at the same instantaneous voltage.
This is a steady-state selection proof, not a startup/time-domain simulator.
"""
from pathlib import Path
from itertools import product
import hashlib,json,xml.etree.ElementTree as E

P=Path(__file__).resolve().parent
UNSPEC='unspecified';OFF='unpowered';Z='Hi-Z'

def select(configuration,vin1,vin2,pr_high,mode_v=None):
    """Literal seven rows of TI 7.3.1; do not fill unspecified conditions."""
    if max(vin1,vin2)==0:return OFF
    if max(vin1,vin2)<1.6:return UNSPEC
    if max(vin1,vin2)>5.5:return UNSPEC
    if pr_high is None:return UNSPEC
    if configuration=='MODE=VIN1':
        chosen='VIN1' if pr_high else 'VIN2'
    elif configuration=='external':
        if mode_v is None or not 0<=mode_v<=5.5:return UNSPEC
        if mode_v>=1:chosen='VIN1' if pr_high else 'VIN2'
        elif mode_v<=.35:
            if pr_high:return Z
            if vin1==vin2:return UNSPEC
            chosen='VIN1' if vin1>vin2 else 'VIN2'
        else:return UNSPEC
    else:raise AssertionError(configuration)
    return chosen if (vin1 if chosen=='VIN1' else vin2)>=1.6 else UNSPEC

def u40_selection(pins,vin1,vin2,pr_high):
    if pins['U40.5']==pins['U40.3']:
        return select('MODE=VIN1',vin1,vin2,pr_high)
    if pins['U40.5']=='GND_USB':
        return select('external',vin1,vin2,pr_high,0)
    raise AssertionError('Unvalidated U40 MODE topology')

def run():
    tree=E.parse(P/'qualified15.net')
    pins={p.attrib['ref']+'.'+p.attrib['pin']:n.attrib['name'].rsplit('/',1)[-1] for n in tree.findall('./nets/net') for p in n}
    cs={c.attrib['ref']:c for c in tree.findall('./components/comp')}
    roles={c.findtext('./fields/field[@name="Role"]'):r for r,c in cs.items()}
    def resistor(role):
        import re
        return float(re.search(r' ([\d.]+)ohm',cs[roles['R_'+role]].findtext('value'))[1])
    assert pins['U40.3']==pins['U40.5']=='AON_USB_LIMITED'
    assert pins['U40.4']=='AON_PRIORITY' and pins['U40.6']=='BOOST_3V9'
    assert pins['U7.1']==pins['U7.3']=='AON_RAW'
    assert pins[roles['R_AON_FEED']+'.1']=='VBUS_RAW'
    assert pins[roles['R_AON_FEED']+'.2']==pins['U40.3']
    assert (resistor('AON_FEED'),resistor('AON_PRIORITY_TOP'),resistor('AON_PRIORITY_BOTTOM'))==(330,22100,10000)
    # Complete documented table, each row independently exercised.
    fixtures=[('MODE=VIN1',4.4,0,True,None,'VIN1'),
              ('MODE=VIN1',0,3.9,False,None,'VIN2'),
              ('external',4.4,0,True,2.5,'VIN1'),
              ('external',0,3.9,False,2.5,'VIN2'),
              ('external',4.4,3.9,True,0,Z),
              ('external',4.4,3.9,False,0,'VIN1'),
              ('external',0,3.9,False,0,'VIN2')]
    for cfg,a,b,pr,m,want in fixtures:assert select(cfg,a,b,pr,m)==want
    assert select('external',4.4,3.9,False,.6)==UNSPEC
    assert select('external',4.4,4.4,False,0)==UNSPEC
    assert select('MODE=VIN1',0,0,False)==OFF
    assert select('MODE=VIN1',2.8,0,False)==UNSPEC
    tol=.001+100*25e-6
    thresholds=[];pr_at_source=[];qualified=[]
    for a,b,ileak,vref in product((-tol,tol),(-tol,tol),(-.1e-6,.1e-6),(.92,1.08)):
        top=resistor('AON_PRIORITY_TOP')*(1+a);bot=resistor('AON_PRIORITY_BOTTOM')*(1+b)
        thresholds.append(vref*(1+top/bot)+ileak*top)
        vin=4.4-.002*resistor('AON_FEED')*(1+tol)
        pr=(vin-ileak*top)/(1+top/bot);pr_at_source.append(pr)
        assert pr>vref
        for boost in [0,3.8,4.1]:
            got=u40_selection(pins,vin,boost,pr>vref)
            assert got=='VIN1';qualified.append(got)
    # Old physical wiring as a mutation: don't mutate the expected result.
    old=dict(pins);old['U40.5']='GND_USB'
    vin=4.4-.002*330*(1+tol)
    negative=[]
    for label,boost in [('valid-source empty-cap coldboot',0),('valid-source hotattach',3.9)]:
        before=u40_selection(old,0,boost,False)
        bad=u40_selection(old,vin,boost,True)
        fixed=u40_selection(pins,vin,boost,True)
        assert bad==Z and fixed=='VIN1'
        negative.append({'scenario':label,'old_before':before,'old_after':bad,'fixed_after':fixed,'old_guaranteed_AON_path':False})
    # Every combination of absent/low/priority-valid raw and absent/valid boost.
    states=[]
    for vin,boost in product([0,1.5,2.8,3.6,vin,5.5],[0,1.5,3.8,4.1]):
        # Representative values are strictly outside the entire threshold range.
        high=vin>max(thresholds)
        assert high or vin<min(thresholds)
        got=u40_selection(pins,vin,boost,high)
        if high:assert got=='VIN1'
        elif boost>=1.6:assert got=='VIN2'
        else:assert got in [OFF,UNSPEC]
        states.append({'VIN1_V':vin,'boost_V':boost,'selection':got})
    # MODE and PR1 pin loads added by this correction are bounded by 6.5.
    # IQ max4.4uA at VIN1>VIN2+.1; max4.5uA VIN2 at reverse condition.
    # Use sum of both maxima +2.1uA standby + .1uA each pin conservatively.
    # This is a small specified part of the pre-existing 2mA total allocation.
    divider_max=5.5/((22100+10000)*(1-tol))
    mux_control_max=4.4e-6+4.5e-6+2.1e-6+2*.1e-6
    load_limit=(4.4-max(thresholds))/(330*(1+tol))
    assert divider_max+mux_control_max<.000184
    assert .002<load_limit
    assert vin<=5.5 and 5.5*10000*(1+tol)/(22100*(1-tol)+10000*(1+tol))<5.5
    # Main mux may select VIN1 early; it is NOT an off-state barrier.
    assert pins['U19.5']=='AON_2V5' and pins['U19.4']=='SOURCE_VALID'
    main=[]
    for mode in [0,.2,.35,.6,1,1.65,2.5]:
        for pr in [False,True]:
            got=select('external',4.4,0,pr,mode)
            if mode<=.35:assert got==(Z if pr else 'VIN1')
            if .35<mode<1:assert got==UNSPEC
            if mode>=1:assert got==('VIN1' if pr else UNSPEC)
            main.append({'AON_MODE_V':mode,'PR1_high':pr,'empty_cap_selection':got})
    datasheet=P.parents[1]/'source-cache/tps2116.pdf'
    txt=P.parents[1]/'source-cache/tps2116.txt'
    assert hashlib.sha256(datasheet.read_bytes()).hexdigest()=='5babd88afb84e2e65c9c0da23b75f85758c0c730e34102a0fb746ac9573ed1d5'
    report={'status':'PASS source-table/topology/DC regression; no transient guarantee',
      'primary':{'document':'TI SLVSFG1A May2021','pdf':str(datasheet.relative_to(P.parents[4])),
                 'pdf_sha256':hashlib.sha256(datasheet.read_bytes()).hexdigest(),'text_sha256':hashlib.sha256(txt.read_bytes()).hexdigest(),
                 'sections':'6.1 absolute controls -0.3..6V; 6.3 inputs1.6..5.5V controls0..5.5V; 6.5 leakage/IQ/VREF; 7.3.1 seven truth rows; 7.3.2 softstart; 7.4 collapse',
                 'cached_text_line_ranges':{'absolute':[116,125],'operating':[153,164],'truth_table':[583,603]}},
      'documented_truth_rows_tested':len(fixtures),'qualified_source_corner_cases':len(qualified),
      'raw_boost_cases':states,'old_wiring_negative_regressions':negative,
      'priority_input_threshold_min_V':min(thresholds),'priority_input_threshold_max_V':max(thresholds),
      'qualified_raw_V':4.4,'total_AON_feed_allocation_A':.002,
      'AON_VIN1_min_under_allocation_V':4.4-.002*330*(1+tol),'PR1_min_under_allocation_V':min(pr_at_source),
      'priority_load_at_threshold_max_A':load_limit,'divider_max_A':divider_max,
      'conservative_mux_IQ_standby_control_sum_A':mux_control_max,
      'remaining_2mA_allocation_for_LDO_logic_pullups_A':.002-divider_max-mux_control_max,
      'main_U19_ramp_states':main,
      'limitations':['2mA total steady AON load is an engineering allocation, not a measured or full switching-current maximum. Separate max IQ values retain their TI test conditions.',
        'Selected input below1.6V, equal inputs in manual low mode, PR1 at threshold and MODE external .35..1V have no table guarantee.',
        'U19 may feed BACKUP_RAW early while MODE low; source qualification/buck enable are separate. AON gates below1.65V remain unspecified.',
        'U40 priority is raw-fed before AON exists; no self-powered external MODE bias. Cold startup U40 output softstart current/time maximum unspecified.',
        'Switching/RCB/hold-up, fast raw collapse per7.4, ramp, loadsteps, ESR and thermal require bench validation. No startup gate closed.'],
      'manufacturing_release':False}
    (P/'mux-mode-proof.json').write_text(json.dumps(report,indent=2)+'\n')
    return report

if __name__=='__main__':
    result=run()
    print(json.dumps({k:result[k] for k in ['status','documented_truth_rows_tested','qualified_source_corner_cases','old_wiring_negative_regressions','priority_input_threshold_max_V','AON_VIN1_min_under_allocation_V','priority_load_at_threshold_max_A']},indent=2))
